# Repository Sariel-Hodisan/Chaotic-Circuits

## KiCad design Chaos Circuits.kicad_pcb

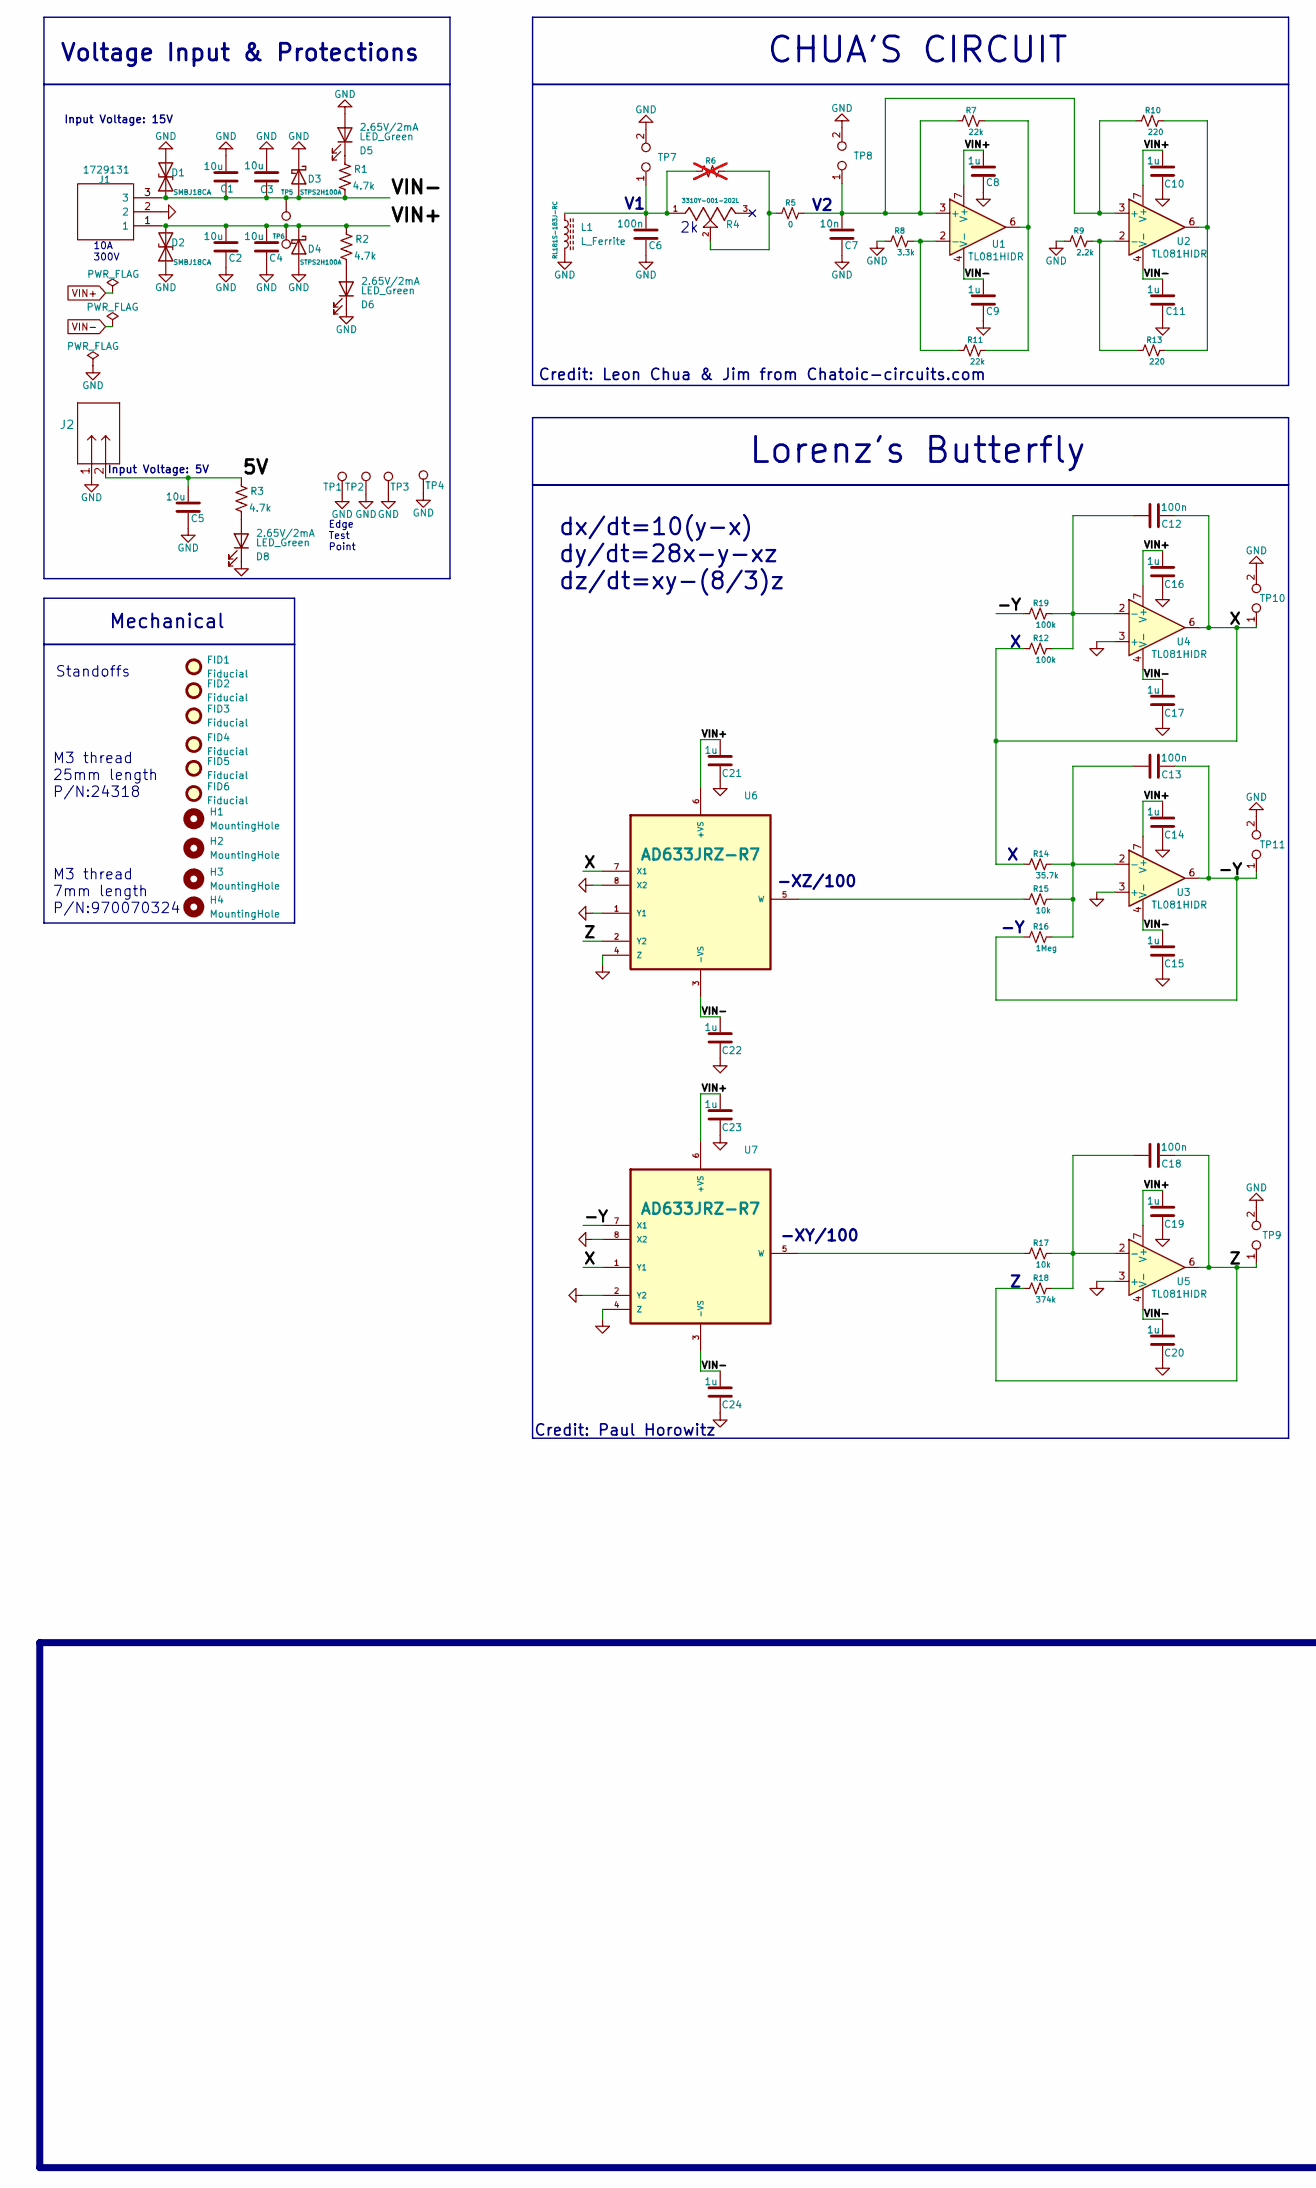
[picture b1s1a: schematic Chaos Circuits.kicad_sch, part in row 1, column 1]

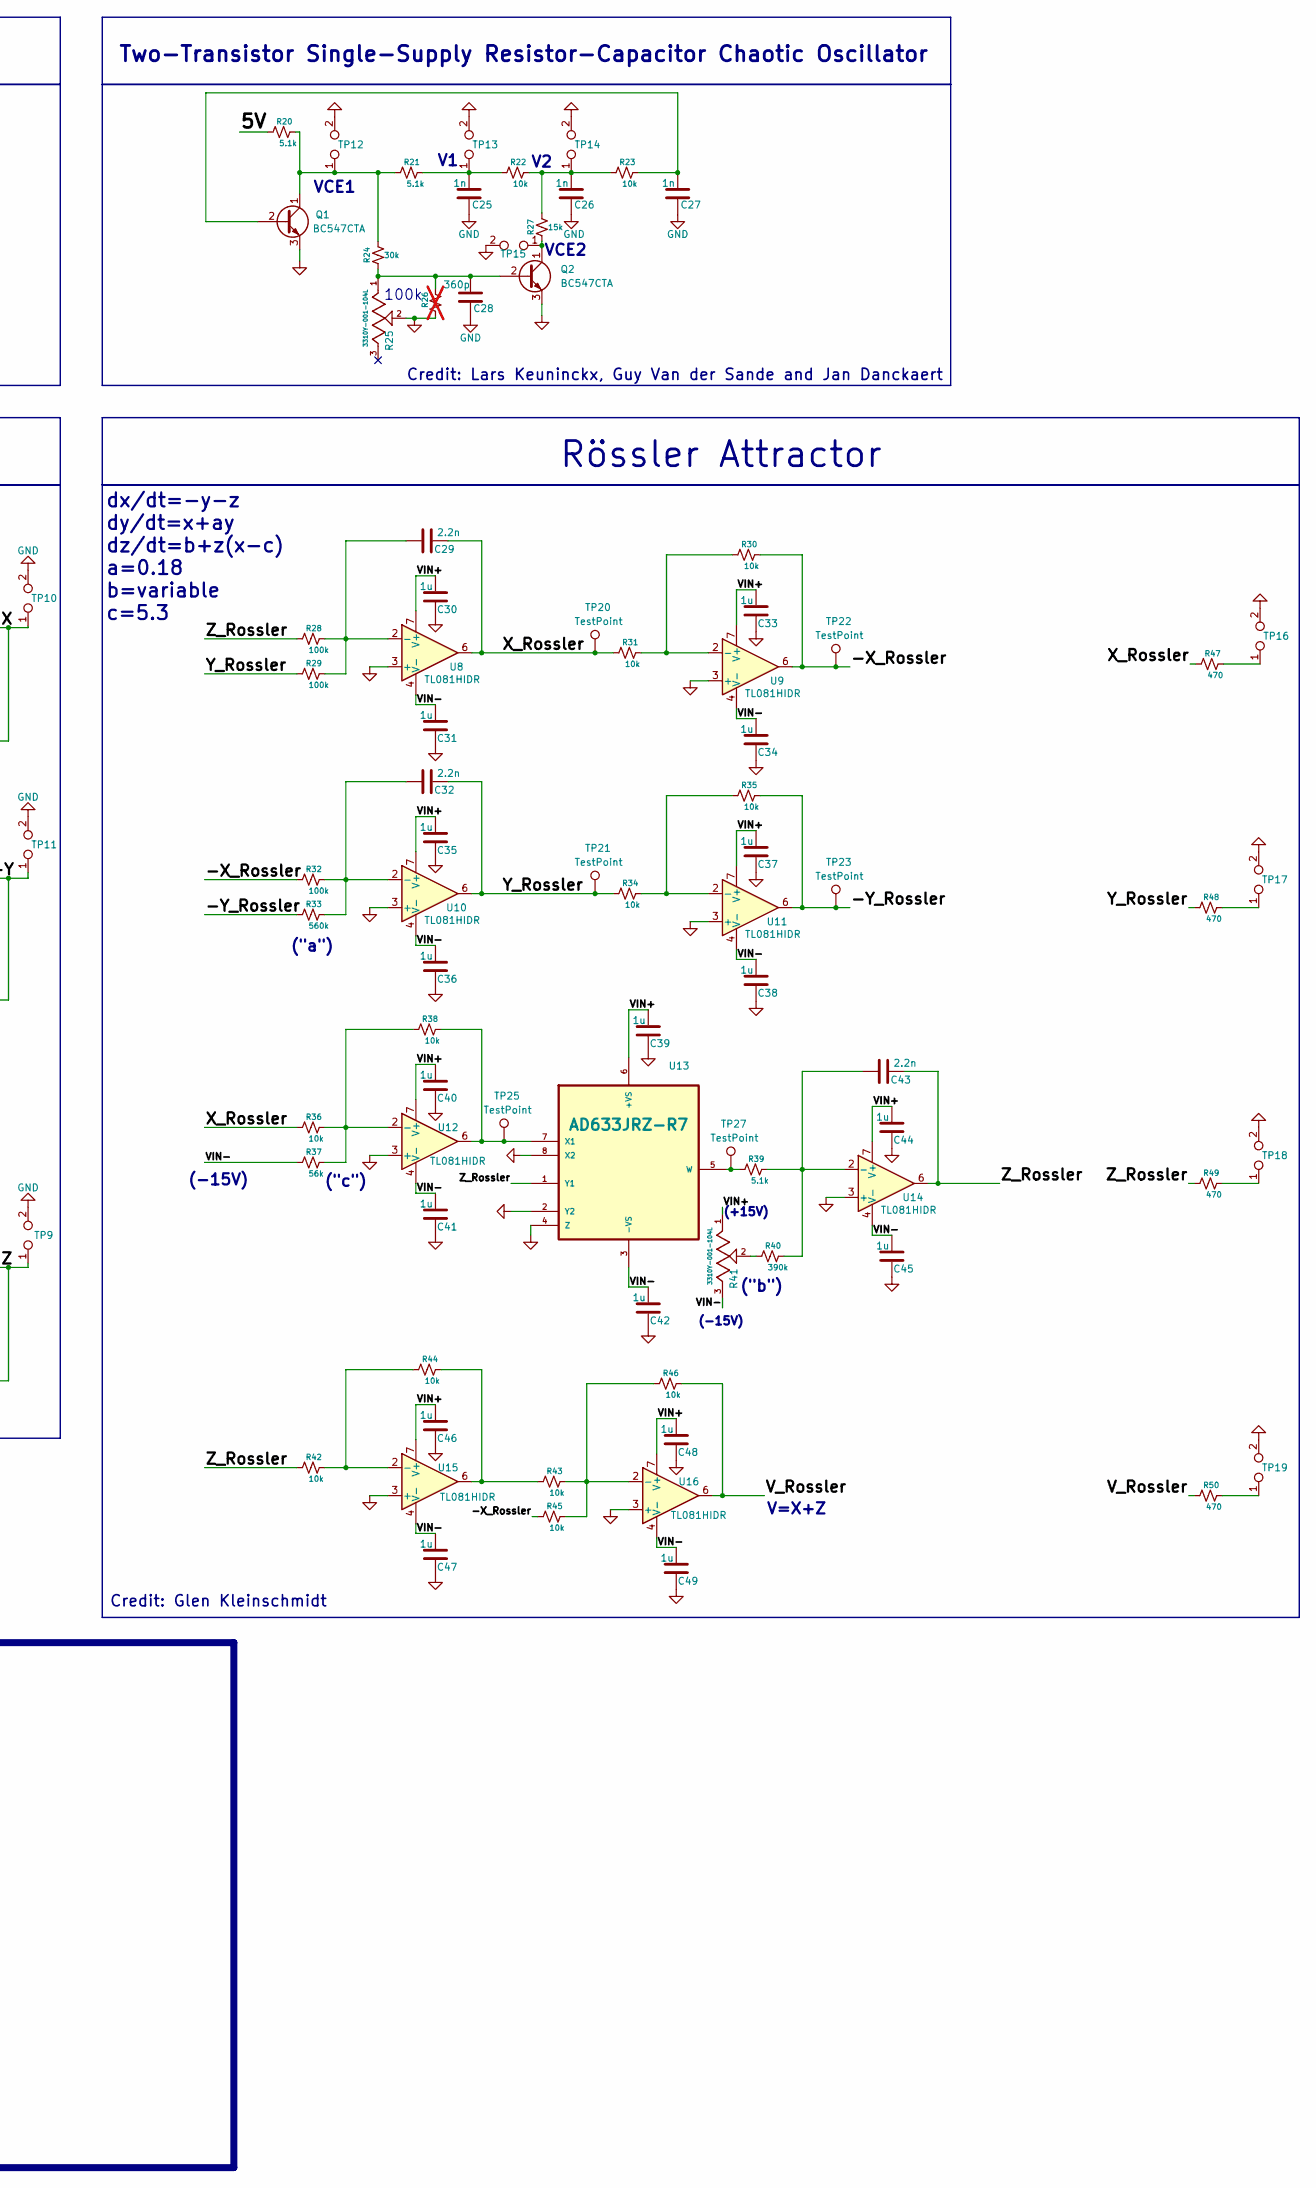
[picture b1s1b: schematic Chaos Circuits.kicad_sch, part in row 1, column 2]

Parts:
C1, C2, C3, C4, C5: 10u; C_1206_3216Metric; Tolerance 10%; Voltage Rating 50V; Part Number GCM31CD71H106KE36K
C6, C12, C13, C18: 100n; C_0805_2012Metric; Tolerance 5%; Voltage Rating 50V; Part Number C0805C104J5RAC7800
C7: 10n; C_0805_2012Metric; Tolerance 1%; Voltage Rating 50V; Part Number C0805C103F5GAC7800
C8, C9, C10, C11, C14, C15, C16, C17, C19, C20, C21, C22, C23, C24, C30, C31, C33, C34, C35, C36, C37, C38, C39, C40, C41, C42, C44, C45, C46, C47, C48, C49: 1u; C_0805_2012Metric; Tolerance 10%; Voltage Rating 50V; Part Number CL21B105KBFNNNE
C25, C26, C27: 1n; C_0805_2012Metric; Tolerance 5%; Voltage Rating 50V; Part Number C0805C102J5GAC7800
C28: 360p; C_0805_2012Metric; Tolerance 5%; Voltage Rating 50V; Part Number CC0805JRNPO9BN361
C29, C32, C43: 2.2n; C_0805_2012Metric; Tolerance 5%; Voltage Rating 50V; Part Number CL21B222JBANNNC
D1, D2: SMBJ18CA; D_SMB; Part Number SMBJ18CA
D3, D4: STPS2H100A; SMA_STM; Voltage Rating 100V 2A; Part Number STPS2H100A
D5, D6, D8: LED_Green; LED_1206_3216Metric_Pad1.42x1.75mm_HandSolder; Voltage Rating 2.65V/2mA; Part Number APT3216LZGCK
FID1, FID2, FID3, FID4, FID5, FID6: Fiducial; Fiducial_1mm_Mask2mm
H1, H2, H3, H4: MountingHole; MountingHole_3.5mm_Pad_TopBottom
J1: 1729131; Manufacturer_Part_Number 1729131; Mouser Part Number 651-1729131
J2: 796681-2; 796681-2_TEC; Part Number 796681-2
L1: L_Ferrite; L_Radial_D10.5mm_P5.00mm_Abacron_AISR-01; Power Rating 21mA; Part Number RL181S-183J-RC
Q1, Q2: BC547CTA; TO-92_Inline; Part Number BC547CTA
R1, R2, R3: 4.7k; R_0603_1608Metric; Power Rating 0.1W; Tolerance 1%; Part Number RC0603FR-074K7L
R4: 3310Y-001-202L; TRIM_3310Y-001-202L; Power Rating 0.25W; Part Number 3310Y-001-202L
R5: 0; R_1206_3216Metric; Power Rating 1/4W; Part Number RMCF1206ZT0R00
R6, R26: 0; R_1206_3216Metric; Power Rating 1/4W; Part Number RMCF1206ZT0R00; not fitted
R7, R11: 22k; R_0805_2012Metric; Power Rating 1/8W; Tolerance 1%; Part Number CRCW080522K0FKEAC
R8: 3.3k; R_0805_2012Metric; Power Rating 1/8W; Tolerance 1%; Part Number CRCW08053K30FKEAC
R9: 2.2k; R_0805_2012Metric; Power Rating 1/8W; Tolerance 1%; Part Number CRG0805F2K2
R10, R13: 220; R_0805_2012Metric; Power Rating 1/8W; Tolerance 1%; Part Number CRG0805F220R
R12, R19, R28, R29, R32: 100k; R_0805_2012Metric; Power Rating 1/8W; Tolerance 0.1%; Part Number ERA-6AEB104V
R14: 35.7k; R_0805_2012Metric; Power Rating 1/8W; Tolerance 0.1%; Part Number ERA-6AEB3572V
R15, R17, R22, R23, R30, R31, R34, R35, R36, R38, R42, R43, R44, R45, R46: 10k; R_0805_2012Metric; Power Rating 1/8W; Tolerance 0.1%; Part Number RG2012P-103-B-T5
R16: 1Meg; R_0805_2012Metric; Power Rating 1/8W; Tolerance 0.1%; Part Number RT0805BRD071ML
R18: 374k; R_0805_2012Metric; Power Rating 1/8W; Tolerance 0.1%; Part Number YAGEO
R20, R21, R39: 5.1k; R_0805_2012Metric; Power Rating 1/8W; Tolerance 1%; Part Number RC0805FR-075K1L
R24: 30k; R_0805_2012Metric; Power Rating 1/8W; Tolerance 1%; Part Number CRG0805F30K
R25, R41: 3310Y-001-104L; TRIM_3310Y-001-202L; Power Rating 0.25W; Part Number 3310Y-001-104L
R27: 15k; R_0805_2012Metric; Power Rating 1/8W; Tolerance 1%; Part Number CRG0805F15K
R33: 560k; R_0805_2012Metric; Power Rating 1/8W; Tolerance 1%; Part Number RC0805FR-07560KL
R37: 56k; R_0805_2012Metric; Power Rating 1/8W; Tolerance 1%; Part Number RC0805FR-0756KL
R40: 390k; R_0805_2012Metric; Power Rating 1/8W; Tolerance 1%; Part Number ERJ-6ENF3903V
R47, R48, R49, R50: 470; R_0805_2012Metric; Power Rating 1/8W; Tolerance 1%; Part Number RC0805FR-07470RL
TP1: TestPoint; TestPoint_THTPad_D3.0mm_Drill1.5mm
TP2, TP3, TP4, TP5, TP6: TestPoint; TestPoint_THTPad_D2.0mm_Drill1.0mm
TP7, TP8, TP9, TP10, TP11, TP12, TP13, TP14, TP15, TP16, TP17, TP18, TP19: TestPoint_2Pole; TestPoint_Bridge_Pitch7.62mm_Drill1.3mm
TP20, TP21, TP22, TP23, TP25, TP27: TestPoint; TestPoint_Keystone_5005-5009_Compact; Part Number 5005
U1, U2, U3, U4, U5, U8, U9, U10, U11, U12, U14, U15, U16: TL081HIDR; SOIC8_D_TEX; Part Number TL081HIDR
U6, U7, U13: AD633JRZ-R7; AD633; Part Number AD633JRZ-R7

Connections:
/5V: C5.1, J2.2, R3.1, R20.1
/-X_Rossler: R30.2, R32.1, R45.1, TP22.1, U9.6
/-Y: C13.2, R16.1, R19.1, TP11.1, U3.6, U7.7 (X1)
/-Y_Rossler: R33.1, R35.2, TP23.1, U11.6
/V_Rossler: R46.2, R50.1, U16.6
/X: C12.2, R12.1, R14.1, TP10.1, U4.6, U6.7 (X1), U7.1 (Y1)
/X_Rossler: C29.2, R31.1, R36.1, R47.1, TP20.1, U8.6
/Y_Rossler: C32.2, R29.1, R34.1, R48.1, TP21.1, U10.6
/Z: C18.2, R18.1, TP9.1, U5.6, U6.2 (Y2)
/Z_Rossler: C43.2, R28.1, R42.1, R49.1, U13.1 (Y1), U14.6
GND: C1.1, C2.2, C3.1, C4.2, C5.2, C6.2, C7.2, C8.2, C9.2, C10.2, C11.2, C14.2, C15.2, C16.2, C17.2, C19.2, C20.2, C21.2, C22.2, C23.2, C24.2, C25.2, C26.2, C27.2, C28.2, C30.2, C31.2, C33.2, C34.2, C35.2, C36.2, C37.2, C38.2, C39.2, C40.2, C41.2, C42.2, C44.2, C45.2, C46.2, C47.2, C48.2, C49.2, D1.2 (A2), D2.1 (A1), D3.1 (K), D4.2 (A), D5.2 (A), D6.1 (K), D8.1 (K), J1.2, J2.1, L1.2, Q1.3 (E), Q2.3 (E), R8.1, R9.1, R25.2, R26.1, TP1.1, TP2.1, TP3.1, TP4.1, TP7.1, TP7.2, TP8.1, TP8.2, TP9.1, TP9.2, TP10.1, TP10.2, TP11.1, TP11.2, TP12.1, TP12.2, TP13.1, TP13.2, TP14.1, TP14.2, TP15.1, TP15.2, TP16.1, TP16.2, TP17.1, TP17.2, TP18.1, TP18.2, TP19.1, TP19.2, U3.3 (+), U4.3 (+), U5.3 (+), U6.1 (Y1), U6.4 (Z), U6.8 (X2), U7.2 (Y2), U7.4 (Z), U7.8 (X2), U8.3 (+), U9.3 (+), U10.3 (+), U11.3 (+), U12.3 (+), U13.2 (Y2), U13.4 (Z), U13.8 (X2), U14.3 (+), U15.3 (+), U16.3 (+)
unnamed: C6.1, L1.1, R4.1, R6.1, TP7.1
unnamed: C25.1, R21.2, R22.1, TP13.1
unnamed: C26.1, R22.2, R23.1, R27.2, TP14.1
unnamed: D5.1 (K), R1.1
unnamed: D6.2 (A), R2.2
unnamed: D8.2 (A), R3.2
unnamed: C27.1, Q1.2 (B), R23.2
unnamed: Q1.1 (C), R20.2, R21.1, R24.2, TP12.1
unnamed: C28.1, Q2.2 (B), R24.1, R25.1, R26.2
unnamed: Q2.1 (C), R27.1, TP15.1
unnamed: R4.2, R5.1, R6.2
unnamed: R10.2, R13.2, U2.6
unnamed: R7.2, R11.2, U1.6
unnamed: R40.1, R41.2
unnamed: R43.1, R44.2, U15.6
unnamed: R47.2, TP16.1
unnamed: R48.2, TP17.1
unnamed: R49.2, TP18.1
unnamed: R50.2, TP19.1
unnamed: C7.1, R5.2, R7.1, R10.1, TP8.1, U1.3 (+), U2.3 (+)
unnamed: R8.2, R11.1, U1.2 (-)
unnamed: R9.2, R13.1, U2.2 (-)
unnamed: C13.1, R14.2, R15.2, R16.2, U3.2 (-)
unnamed: C12.1, R12.2, R19.2, U4.2 (-)
unnamed: C18.1, R17.2, R18.2, U5.2 (-)
unnamed: R15.1, U6.5 (W)
unnamed: R17.1, U7.5 (W)
unnamed: C29.1, R28.2, R29.2, U8.2 (-)
unnamed: R30.1, R31.2, U9.2 (-)
unnamed: C32.1, R32.2, R33.2, U10.2 (-)
unnamed: R34.2, R35.1, U11.2 (-)
unnamed: R36.2, R37.2, R38.1, U12.2 (-)
unnamed: R39.1, TP27.1, U13.5 (W)
unnamed: R38.2, TP25.1, U12.6, U13.7 (X1)
unnamed: C43.1, R39.2, R40.2, U14.2 (-)
unnamed: R42.2, R44.1, U15.2 (-)
unnamed: R43.2, R45.2, R46.1, U16.2 (-)
VIN+: C2.1, C4.1, C8.1, C10.1, C14.1, C16.1, C19.1, C21.1, C23.1, C30.1, C33.1, C35.1, C37.1, C39.1, C40.1, C44.1, C46.1, C48.1, D2.2 (A2), D4.1 (K), J1.1, R2.1, R41.1, TP6.1, U1.7 (V+), U2.7 (V+), U3.7 (V+), U4.7 (V+), U5.7 (V+), U6.6 (+VS), U7.6 (+VS), U8.7 (V+), U9.7 (V+), U10.7 (V+), U11.7 (V+), U12.7 (V+), U13.6 (+VS), U14.7 (V+), U15.7 (V+), U16.7 (V+)
VIN-: C1.2, C3.2, C9.1, C11.1, C15.1, C17.1, C20.1, C22.1, C24.1, C31.1, C34.1, C36.1, C38.1, C41.1, C42.1, C45.1, C47.1, C49.1, D1.1 (A1), D3.2 (A), J1.3, R1.2, R37.1, R41.3, TP5.1, U1.4 (V-), U2.4 (V-), U3.4 (V-), U4.4 (V-), U5.4 (V-), U6.3 (-VS), U7.3 (-VS), U8.4 (V-), U9.4 (V-), U10.4 (V-), U11.4 (V-), U12.4 (V-), U13.3 (-VS), U14.4 (V-), U15.4 (V-), U16.4 (V-)

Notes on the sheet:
Input Voltage: 5V
Credit: Paul Horowitz
Voltage Input & Protections
Two-Transistor Single-Supply Resistor-Capacitor Chaotic Oscillator
Rössler Attractor
10A 300V
100k
dx/dt=-y-z dy/dt=x+ay dz/dt=b+z(x-c) a=0.18 b=variable c=5.3
("b")
("c")
(-15V)
Credit: Lars Keuninckx, Guy Van der Sande and Jan Danckaert
-XY/100
VCE2
VCE1
(+15V)
Edge Test Point
Mechanical
Input Voltage: 15V
("a")
Standoffs
-XZ/100
dx/dt=10(y-x) dy/dt=28x-y-xz dz/dt=xy-(8/3)z
Credit: Leon Chua & Jim from Chatoic-circuits.com
V=X+Z
M3 thread 25mm length P/N:24318
CHUA'S CIRCUIT
Lorenz's Butterfly
M3 thread 7mm length P/N:970070324
Credit: Glen Kleinschmidt

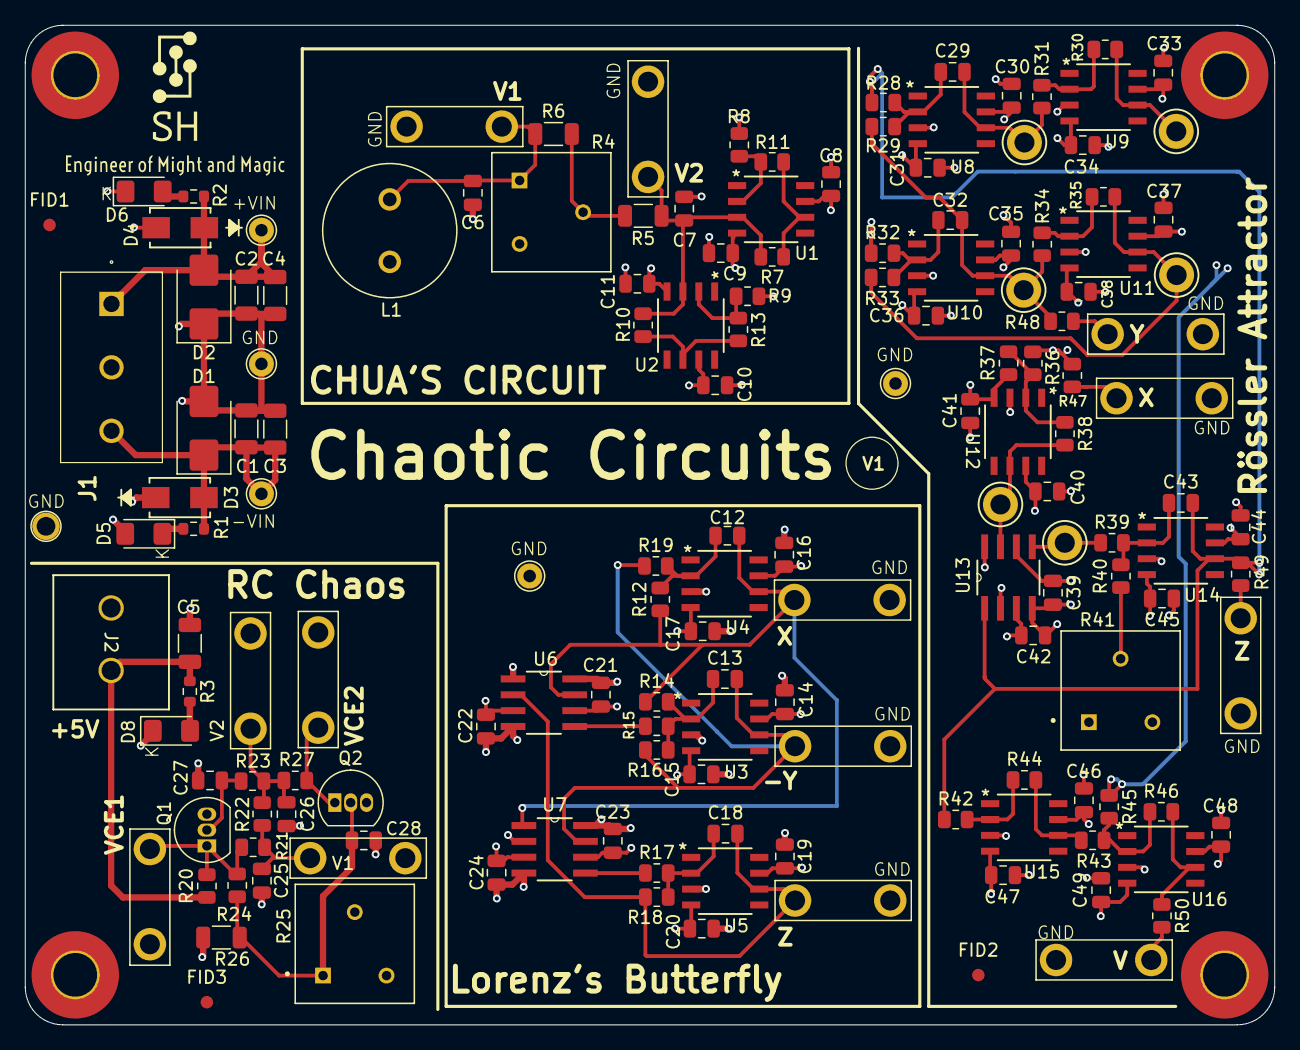
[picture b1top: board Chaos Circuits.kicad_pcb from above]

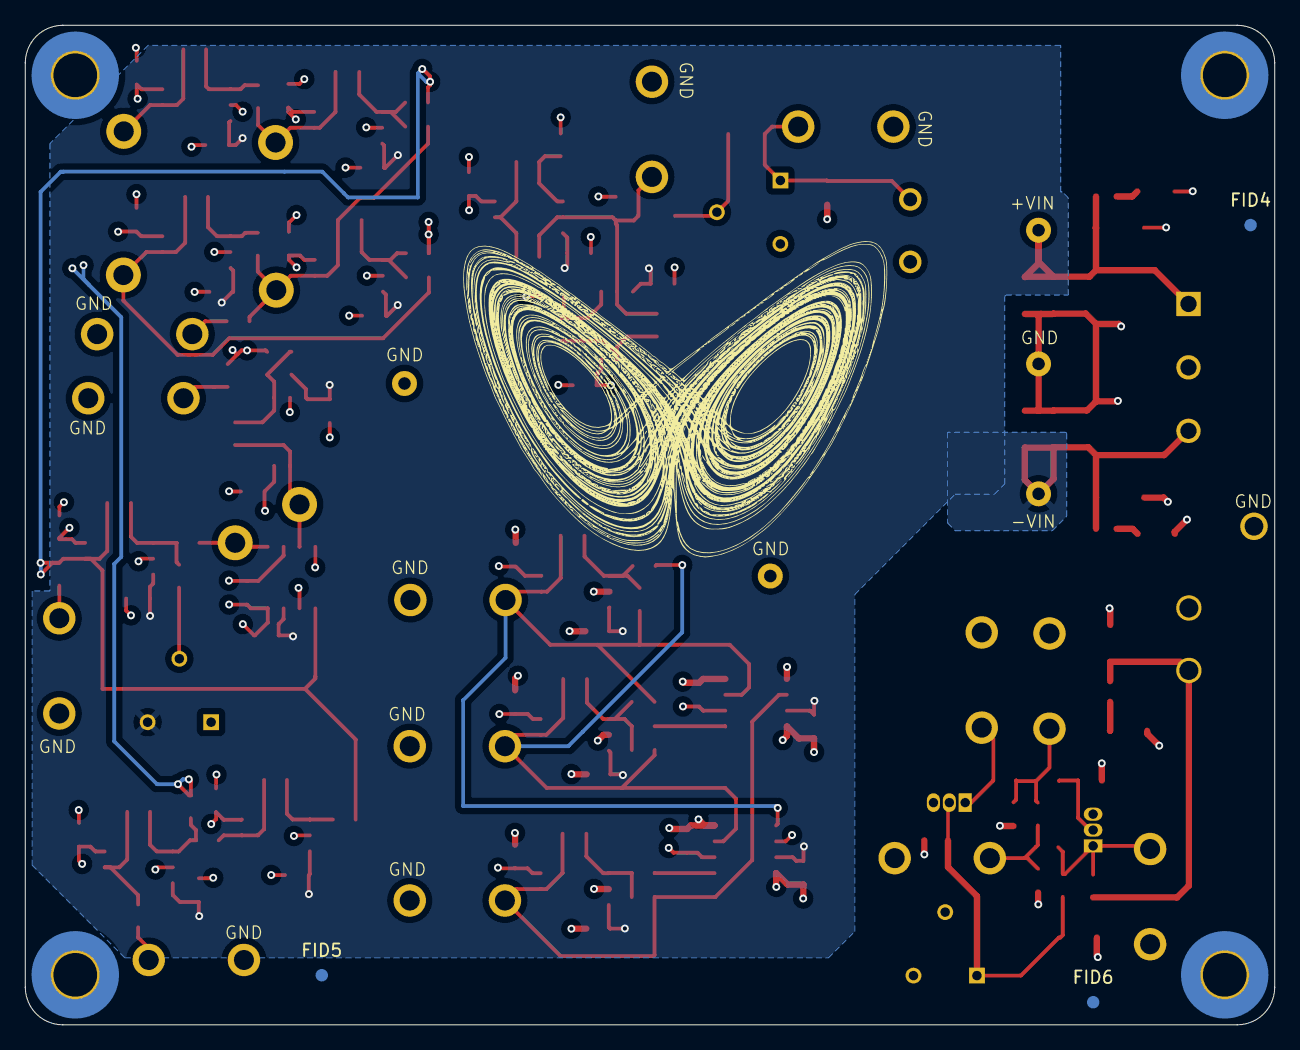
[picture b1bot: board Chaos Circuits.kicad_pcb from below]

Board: 4 copper layers, 100.0 x 80.0 mm, 162 parts (3 on the bottom side), 50 nets.

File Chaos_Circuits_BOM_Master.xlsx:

Item # | *Designator | *Qty | Manufacturer | *Mfg Part # | Description / Value | *Package/Footprint | Type | Your Instructions / Notes
1 | C1,C2,C3,C4,C5 | 5 | Murata | GCM31CD71H106KE36K | 10 µF ±10% 50V Ceramic Capacitor X7T 1206 (3216 Metric) | 1206 | SMT
2 | C6,C12,C13,C18 | 4 | Kemet | C0805C104J5RAC7800 | 0.1 µF ±5% 50V Ceramic Capacitor X7R 0805 (2012 Metric) | 0805 | SMT
3 | C7 | 1 | Kemet | C0805C103F5GAC7800 | 10000 pF ±1% 50V Ceramic Capacitor C0G, NP0 0805 (2012 Metric) | 0805 | SMT
4 | C8,C9,C10,C11,C14,C15,C16,C17,C19,C20,C21,C22,C23,C24,C30,C31,C33,C34,C35,C36,C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 | 32 | Samsung Electro-Mechanics | CL21B105KBFNNNE | 1 µF ±10% 50V Ceramic Capacitor X7R 0805 (2012 Metric) | 0805 | SMT
5 | C25,C26,C27 | 3 | KEMET | C0805C102J5GAC7800 | 1000 pF ±5% 50V Ceramic Capacitor C0G, NP0 0805 (2012 Metric) | 0805 | SMT
6 | C28 | 1 | YAGEO | CC0805JRNPO9BN361 | 360 pF ±5% 50V Ceramic Capacitor C0G, NP0 0805 (2012 Metric) | 0805 | SMT
7 | C29,C32,C43 | 3 | Samsung Electro-Mechanics | CL21B222JBANNNC | 2200 pF ±5% 50V Ceramic Capacitor X7R 0805 (2012 Metric) | 0805 | SMT
8 | D1,D2 | 2 | Littelfuse Inc. | SMBJ18CA | 24.4V Clamp 24.6A Ipp Tvs Diode Surface Mount DO-214AA (SMBJ) | SMB | SMT
9 | D3,D4 | 2 | STMicroelectronics | STPS2H100A | Diode 100 V 2A Surface Mount SMA (DO-214AC) | SMA | SMT
10 | D5,D6,D8 | 3 | Kingbright | APT3216LZGCK | Green 525nm LED Indication - Discrete 2.65V 1206 | 1206 | SMT
11 | J1 | 1 | Phoenix Contact | 1729131 | PCB terminal block, nominal current: 13.5 A, rated voltage (III/2): 400 V, | Connector | TH
12 | J2 | 1 | TE Connectivity AMP Connectors | 796681-2 | 2 Position Wire to Board Terminal Block Horizontal with Board 0.197" (5.00mm) T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 | Connector | TH
13 | L1 | 1 | Bourns Inc. | RL181S-183J-RC | 18 mH Shielded Drum Core, Wirewound Inductor 21 mA 17Ohm Max Radial, Vertical C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 | Radial, Vertical Cylinder | TH
14 | Q1,Q2 | 2 | onsemi | BC547CTA | Bipolar (BJT) Transistor NPN 45 V 100 mA 300MHz 500 mW Through Hole TO-92-3 | TO-92-3 | TH
15 | R1,R2,R3 | 3 | YAGEO | RC0603FR-074K7L | RES 4.7K OHM 1% 1/10W 0603 | 0603 | SMT
16 | R4 | 1 | Bourns Inc. | 3310Y-001-202L | 2k Ohm 1 Gang Linear Panel Mount Potentiometer None 1.0 Kierros Conductive Plas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 | Pot | TH
17 | R5 | 1 | Stackpole Electronics Inc | RMCF1206ZT0R00 | RES 0 OHM JUMPER 1/4W 1206 | 1206 | SMT
18 | R7,R11 | 2 | Vishay Dale | CRCW080522K0FKEAC | RES 22K OHM 1% 1/8W 0805 | 0805 | SMT
19 | R8 | 1 | Vishay Dale | CRCW08053K30FKEAC | RES 3.3K OHM 1% 1/8W 0805 | 0805 | SMT
20 | R9 | 1 | TE Connectivity Passive Product | CRG0805F2K2 | RES SMD 2.2K OHM 1% 1/8W 0805 | 0805 | SMT
21 | R10,R13 | 2 | TE Connectivity Passive Product | CRG0805F220R | RES SMD 220 OHM 1% 1/8W 0805 | 0805 | SMT
22 | R12,R19,R28,R29,R32 | 5 | Panasonic Electronic Components | ERA-6AEB104V | RES SMD 100K OHM 0.1% 1/8W 0805 | 0805 | SMT
23 | R14 | 1 | Panasonic Electronic Components | ERA-6AEB3572V | RES SMD 35.7K OHM 0.1% 1/8W 0805 | 0805 | SMT
24 | R15,R17,R22,R23,R30,R31,R34,R35,R36,R38,R42,R43,R44,R45,R46 | 15 | Susumu | RG2012P-103-B-T5 | RES SMD 10K OHM 0.1% 1/8W 0805 | 0805 | SMT
25 | R16 | 1 | YAGEO | RT0805BRD071ML | RES SMD 1M OHM 0.1% 1/8W 0805 | 0805 | SMT
26 | R18 | 1 | YAGEO | YAGEO | RES SMD 374K OHM 0.1% 1/8W 0805 | 0805 | SMT
27 | R20,R21,R39 | 3 | YAGEO | RC0805FR-075K1L | RES 5.1K OHM 1% 1/8W 0805 | 0805 | SMT
28 | R24 | 1 | TE Connectivity Passive Product | CRG0805F30K | RES SMD 30K OHM 1% 1/8W 0805 | 0805 | SMT
29 | R25,R41 | 2 | Bourns Inc. | 3310Y-001-104L | 100k Ohm 1 Gang Linear Panel Mount Potentiometer None 1.0 Kierros Conductive Pl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 | Pot | TH
30 | R27 | 1 | TE Connectivity Passive Product | CRG0805F15K | RES SMD 15K OHM 1% 1/8W 0805 | 0805 | SMT
31 | R33 | 1 | YAGEO | RC0805FR-07560KL | RES SMD 100K OHM 0.1% 1/8W 0805 | 0805 | SMT
32 | R37 | 1 | YAGEO | RC0805FR-0756KL | RES 56K OHM 1% 1/8W 0805 | 0805 | SMT
33 | R40 | 1 | Panasonic Electronic Components | ERJ-6ENF3903V | RES SMD 390K OHM 1% 1/8W 0805 | 0805 | SMT
34 | R47,R48,R49,R50 | 4 | YAGEO | RC0805FR-07470RL | RES 470 OHM 1% 1/8W 0805 | 0805 | SMT
35 | U1,U2,U3,U4,U5,U8,U9,U10,U11,U12,U14,U15,U16 | 13 | Texas Instruments | TL081HIDR | J-FET Amplifier 1 Circuit Push-Pull 8-SOIC | 8-SOIC | SMT
36 | U6,U7,U13 | 3 | Analog Devices Inc. | AD633JRZ-R7 | Analog Multiplier 4-Quadrant 8-SOIC | 8-SOIC | SMT
